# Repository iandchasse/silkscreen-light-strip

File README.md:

# Silkscreen light strip

> [!IMPORTANT]
> **AI-generated design. This is an accessory, not part of the Silkscreen PCBA.**
>
> This light strip was designed with substantial AI assistance: its KiCad project is generated by scripts written with
> AI tools. It serves two purposes: a test of what AI tools can and cannot do with a simple electrical design like an
> LED strip, and a functional accessory for the base Silkscreen PCBA. The Silkscreen PCBA itself
> ([silkscreen-pcb](https://github.com/iandchasse/silkscreen-pcb)) was not AI-generated.
>
> See Silkscreen's AI disclosure: https://silkscreenreader.com/ai

**A DIY warm/cool reading light for the [Silkscreen](https://github.com/iandchasse/silkscreen-pcb) e-reader.** It is a thin flex PCB that plugs into the main board's frontlight connector (labelled `J3` on the back of the board), in place of a panel's bonded frontlight. It runs six warm/cool pairs of side-emitting LEDs along the left edge of the e-paper panel, and the light grazes across the page with no light guide.

**One strip fits two readers:**

- the **4.26″** plain `GDEY0426T82`, where the LED bar lies on the panel's left border;
- the **3.68″** 528 × 792 panel of the x3 build, where the bar lies beside the glass and the top pair folds back under it.

**Not released.** The website does not offer the strip or its cases. This repo is the design, its fabrication files and its documents, for anyone who wants to build one.

**The cases** are in [silkscreen-enclosures](https://github.com/iandchasse/silkscreen-enclosures). Each reader's case project can also build a light-strip case, which the strip needs: the tub, and on the 3.68″ also the four bottom keys. Those cases are in development and not released either (see [The cases](#the-cases)).

**Where things are:**

| To | Go to |
|---|---|
| **Order the light strip (rev A, untested)** | [`production/`](production/) and [docs/ORDERING.md](docs/ORDERING.md) |
| **Assemble and fit the strip** | [docs/ASSEMBLY.md](docs/ASSEMBLY.md) |
| **Print a paste stencil** and its card squeegee, one plate (experimental, untested) | [`production/stencil/`](production/stencil/) (`stencil-kit_*.3mf`) and [docs/ASSEMBLY.md §2, option](docs/ASSEMBLY.md#option-3d-printed-paste-stencil-and-oven-reflow-experimental-untested) |
| **The cases** | the light-strip builds in [silkscreen-enclosures](https://github.com/iandchasse/silkscreen-enclosures) (`enclosures/case-426`, `enclosures/case-368`), in development with the strip |
| **Change the strip** | `tools/` (it generates the KiCad project at the root and everything in `docs/` and `production/`); the design is in [docs/DESIGN.md](docs/DESIGN.md) |
| **Read the documents** | the [documents index](#documents) below: design, ordering, assembly, reports, research and reviews |

> **Rev A is untested.** The strip passes ERC, DRC and schematic parity with no findings. Four review rounds have been worked through ([docs/DESIGN.md §8](docs/DESIGN.md#8-verification) lists them; the first round's reports are in [docs/review/](docs/review/)). No board has been built yet. Before you solder a whole strip, diode-test one loose LED ([docs/ASSEMBLY.md](docs/ASSEMBLY.md#1-check-led-polarity-before-anything-else)).

| Flat, LED side (turned 90°) |
|:---:|
|  |

| 4.26″: on the border, around the glass edge | 4.26″: behind the board, into the frontlight connector |
|:---:|:---:|
|  |  |

| 3.68″: beside the panel | 3.68″: top pair folded back under the bar | 3.68″: spare tail looped on the board's back |
|:---:|:---:|:---:|
|  |  |  |

## What it is

- **Where it goes.** The LED bar runs along the panel's left long edge, hidden under the bezel. The strip then sweeps along the bottom border and folds over the bottom glass edge, through the main board's FPC slot, and plugs into the frontlight connector on the back of the board. The fold follows the path of the stock frontlight ribbon.
  - **On the 4.26″** the bar is taped onto the panel's border, and the tail wraps the glass edge in a U.
  - **On the 3.68″** the smaller panel leaves the bar beside its glass, on a shelf in the front shell at the panel-front plane. The tail folds over the glass edge straight into the slot.
- **Light.** There are twelve XINGLIGHT side-view LEDs: six `XL-4008WWC` (3000 K) and six `XL-4008UWC` (6000–6500 K). Each is 4.0 × 1.4 mm and 0.8 mm tall. They sit in six tight warm/cool pairs, 6.6 mm apart within a pair, so both colours light the same patch of page. Each LED's face points across the screen, parallel to its surface.
- **Two readers, one layout.**
  - The bottom five pairs are 15.55 mm apart, which is the 3.68″ active height divided by five.
  - The top pair sits 17.0 mm above them, on its own stiffener piece, with a 3.6 mm bare **hinge** in between.
  - On the 4.26″ all six pairs light the screen.
  - On the 3.68″ the top pair would stick out past the case, so it folds back under the bar, tape to tape, and its light is hidden.
- **Electrically, it is a stock frontlight.**
  - Each colour is one series string of 6 LEDs, about 17.4 V at 13.3 mA, or about 18.4 V at the driver including the flip-protection diode.
  - Worst case (−10 °C, top Vf bin) is 21.7 V, under the 22 V design ceiling and the driver's 24.25 V over-voltage limit. A high batch (LCSC lists the cool LED at 3.4 V) can pass 22 V in the cold, still under the over-voltage limit; check one string on the bench ([docs/DESIGN.md §2.1](docs/DESIGN.md#21-six-leds-per-string)).
  - The main board's TPS923610 does everything: constant current, dimming and warm/cool select. Only the firmware's "strip open" threshold changes (see below).
- **Flip-proof.** The frontlight connector contacts both faces of a tail, so a tail inserted face-down would mirror the pins. A BAV70W per string blocks that case. The strip stays dark, the driver latches its over-voltage protection, and no LED is reverse-stressed.
- **Built to survive handling.**
  - The bar ends in a full round. Every turn of the outline is a sweeping radius of 1.6–4 mm, and the outer corners span the foot's full 3.5 mm height. Only two places stay small: the contact tab's R0.2 tip corners, which Hirose specifies, and one 1 mm inside corner on the stiffener.
  - The folding section is 5.5 mm wide and carries four 0.4 mm conductors on one copper layer. It has no vias, pads or stiffener, and a copper tear-stop rail runs along each edge.
  - The hinge has no vias, pads, stiffener or tape; its tracks run straight across it.

| | |
|---|---|
| Flat size | 15.1 × 127.6 mm (bar 2.3 mm wide, foot 3.5 mm, tail 5.5 mm, contact tab 3.5 mm over the last 3.8 mm) |
| Build | 2-layer flex, 0.11 mm, 25 µm adhesiveless polyimide, black coverlay, ENIG |
| Stiffeners | PI 0.225 mm in three pieces: the top pair, the bar and foot, and the last 14 mm of the tail (0.30 mm at the contacts). 3M 9077 tape on the two front pieces. |
| Driver output | About 18.4 V typical; 15.9–21.7 V across LED bins and −10 to 60 °C, including the flip-protection diode |
| Current | 13.3 mA nominal and 13.9 mA maximum, set by the main board's 15 Ω current-set resistor (`R37`). One string at a time. |
| Connector | Gold fingers for the main board's frontlight connector (`J3`), a Hirose FH34SRJ-6S-0.5SH(50). Pins: 1 LED_SW, 2 C−, 3/4 NC, 5 LED_SW, 6 W−. |
| Parts | 12 LEDs and 2 BAV70W, plus three wire/probe pads on the tail (`S`, `C`, `W`) |

## Bill of materials

| Qty | Ref | Part | Manufacturer | LCSC |
|---|---|---|---|---|
| 6 | D1–D6 | XL-4008WWC, warm 3000 K side-view LED | XINGLIGHT | C5440667 |
| 6 | D7–D12 | XL-4008UWC, cool 6000–6500 K side-view LED | XINGLIGHT | C2843774 |
| 2 | D13, D14 | BAV70W,115, dual common-cathode diode, SOT-323 | Nexperia | C28064 |

These three LCSC parts are all JLCPCB "Extended" parts. The LEDs are sold only through LCSC. The BAV70W is also a stock DigiKey part.

## The cases

**The light-strip cases are in development and are not released.** The website does not offer them, and no case has been printed around a strip yet. Both readers' cases are in [silkscreen-enclosures](https://github.com/iandchasse/silkscreen-enclosures) (`enclosures/case-426` and `enclosures/case-368`; until 2026-10-21 they lived in this repo). Each project builds a **standard** case and a **light-strip** case, and the two builds share every printed part except:

| | 4.26″ (`enclosures/case-426`) | 3.68″ (`enclosures/case-368`) |
|---|---|---|
| Panel | Plain GDEY0426T82 instead of the FT01C | The x3's 3.68″ panel |
| Differs from the standard build | The tub only | The tub and the four bottom keys (`key-x3ls` stands 0.8 mm taller than `key-x3std`, for the raised face); 13.7 mm deep |
| Front shell | Stops for the thinner plain panel; a raised ceiling over the left border; hold-down pads between the pairs; a wider ribbon gap | Front raised 1.2 mm over x3's, 0.8 over the standard build's (still one flat face); a channel for the bar with the light path to the window; hold-down pads; a neck gap in the chin |

Each case project carries a copy of this strip's outline and fold geometry (`hardware/reference/light-strip/strip-geometry.json`, from `build/geometry.json` here, a git-ignored file that `tools/export_geometry.py` writes with KiCad's Python); [docs/DESIGN.md §4](docs/DESIGN.md#4-geometry-and-fold) has the geometry.

## Using it

### Order it

[docs/ORDERING.md](docs/ORDERING.md) has every file and every field. In short:

- **Files.** Upload `production/silkscreen-light-strip_rev-A_gerbers.zip` to JLCPCB's flex order. It holds the copper, coverlay, silkscreen, paste, outline and drill files, plus the two extra layers `Stiffener_PI0_225.gbr` and `Adhesive_3M9077.gbr`. The bend-zone layer stays out. `production/jlc_bom.csv` and `jlc_cpl.csv` are for an assembled order only; `production/bom.csv` is the parts list for a hand build or an LCSC order; `production/gerbers/` has the loose files, the job file and the drill map.
- **The form.** Flex, 2 layers, quantity 5, FPC 0.11 mm, 1/3 oz copper, black coverlay, white silkscreen, ENIG (1 U″; 2 U″ if you expect to re-insert the tail often), EDA software "Other", stiffener **Polyimide 0.225 mm + 3M Tape 3M9077** selected together in one row, tape pull tab yes (at the foot end), **gold fingers yes, 0.295 mm**, no EMI film, laser cutting, **confirm production file yes**. Paste the 190-character remark from ORDERING.md as it is: JLC does not read the stiffener or tape layers by itself.
- **Bare, soldered by hand** is the recommended path for rev A: it is cheap, and it lets you do the polarity test first. JLC assembly is possible (Panel by JLCPCB, Standard PCBA, a $23.57 fixture and three Extended-part fees); check each LED's window direction and anode position in the preview, not the polarity dot.
- **Cost** is an unverified ballpark only: about $45–75 for 5 bare strips, plus shipping, and about $65–95 more to have JLC assemble 2 of them.

### Assemble and fit

[docs/ASSEMBLY.md](docs/ASSEMBLY.md) covers the polarity check, soldering, a bench test through the three pads (`S`, `C`, `W`), which reader and which case, the fit on the 4.26″ (on the border) and on the 3.68″ (beside the panel, with the top pair folded back), plugging into the frontlight connector, the case, firmware bring-up and troubleshooting.

### Firmware

- Drive it exactly like the stock frontlight ([silkscreen-pcb HARDWARE.md §7](https://github.com/iandchasse/silkscreen-pcb/blob/master/docs/HARDWARE.md#7-frontlight-driver)).
- Enable `ADIM` (`PWM_LED`, IO42) with a HIGH pulse of at least 100 µs (the datasheet minimum is 40 µs), then dim with PWM at 10–200 kHz.
- Change the colour with `COLOR_SEL` (IO40) only while the PWM duty is 0. Keep that pause under about 1 ms, or send the enable pulse again.
- Watch `LED_MONIT` (IO2). A lit strip reads 1.4–2.4 V at full duty.
  - **Open, flipped or missing:** the peak over the first ~1 s after enabling is **2.49 V or more**. The old 2.2 V threshold would call a cold six-LED strip open.
  - The driver then latches off, and `LED_MONIT` sinks back to the off level over several seconds, so record the fault when you first see it.
  - **Shorted LEDs or a bridge:** below 1.30 V at full duty, at least 50 ms after enabling.
  - To restart after a latch, hold `ADIM` low for at least 3 ms.

## What to expect from the light

Light that grazes a page falls off steeply with distance. The geometric model in `tools/optics_sim.py` puts the irradiance 2 mm in from the lit edge at about 230 times the far edge on the 4.26″, and at about 10 times the far edge 20 mm in. The textured front film of an e-paper panel scatters grazing light, which flattens this in practice. The page will still be brighter on the left than the right.

- **On the 4.26″,** six pairs light the edge more evenly than the first layout's five. The ripple along the edge 6 mm in drops from 3.7:1 to 3.1:1.
- **On the 3.68″,** the LED faces are 2.37 mm from the image instead of 1.2 mm. That softens the bright band at the edge; the ripple 3 mm in drops to 5:1.

| Model, one string lit (4.26″ left, 3.68″ right) | Falloff across the page |
|:---:|:---:|
|  |  |

## Documents

| Document | What |
|---|---|
| [`docs/DESIGN.md`](docs/DESIGN.md) | Why the strip is as it is: the main-board fixes, the electrical design (six LEDs per string, the firmware thresholds, the two diodes), the LEDs, the geometry and fold on both readers, robustness, optics, the flex build and DFM, verification and open items. It is current where the dated notes differ. |
| [`docs/ORDERING.md`](docs/ORDERING.md) | The JLCPCB flex order: the files, the form field by field, the remark, the production-file review, bare or assembled, a cost ballpark and a checklist before you pay (also the Fabrication Toolkit route) |
| [`docs/ASSEMBLY.md`](docs/ASSEMBLY.md) | The LED polarity test, soldering, the bench test, which reader and case, fitting on the 4.26″ and the 3.68″, plugging into the frontlight connector, the case, firmware bring-up and troubleshooting |
| [`docs/reports/stencil_slice_check.md`](docs/reports/stencil_slice_check.md) | The paste stencil's slicer read-back: apertures open, membrane printed, pocket empty, print time and filament (toolpath only; nothing has been printed) |
| [`docs/reports/stencil_plate_check.md`](docs/reports/stencil_plate_check.md) | The two stencil-kit projects (`production/stencil/stencil-kit_*.3mf`) read back from a slice: parts and positions, project settings, openings clear on all three cards, the squeegee, the coupon, print time and filament (toolpath only; nothing has been printed) |
| [`docs/reports/stencil_squeegee_check.md`](docs/reports/stencil_squeegee_check.md) | The squeegee's slicer read-back: slot, slits and screw hole open, blade layers, bridges, no floating islands, print time (toolpath only; nothing has been printed) |
| [`docs/reports/design_summary.md`](docs/reports/design_summary.md) | The as-built numbers, regenerated by `tools/report_design.py` on every build |
| [`docs/reports/erc.rpt`](docs/reports/erc.rpt), [`drc.rpt`](docs/reports/drc.rpt) (and `.json`) | The ERC and DRC (with schematic parity) reports from `tools/make_outputs.py`; zero findings |
| [`docs/silkscreen-light-strip_schematic.pdf`](docs/silkscreen-light-strip_schematic.pdf), [`_layout.pdf`](docs/silkscreen-light-strip_layout.pdf) | The schematic, and the layout one layer per page |
| [`docs/mechanical/`](docs/mechanical/) | The flat strip in 3D (`silkscreen-light-strip_flat.step` and `.wrl`) |
| [`docs/images/`](docs/images/) | Renders (flat, folded into each reader, night view), the optics heatmaps and profile, and `optics_summary.json` |
| [`docs/research/electrical-limits.md`](docs/research/electrical-limits.md) (with [`electrical-limits-calc.py`](docs/research/electrical-limits-calc.py)) | Dated 2026-09-24: string voltage and current limits against the TPS923610, cited |
| [`docs/research/fpc-and-jlc-flex.md`](docs/research/fpc-and-jlc-flex.md) | Dated 2026-09-24: the Hirose FH34SRJ tail specification and JLCPCB's flex capabilities |
| [`docs/research/leds.md`](docs/research/leds.md) | Dated 2026-09-24: a survey of side-view warm and cool LEDs on LCSC, and why the XL-4008 pair |
| [`docs/research/mechanical-fit.md`](docs/research/mechanical-fit.md) | Dated 2026-09-24: how the strip fits the board and panel, with the coordinate frames |
| [`docs/review/electrical.md`](docs/review/electrical.md) | Review of 2026-09-25: polarity, nets, the voltage budget, flip and fault behaviour |
| [`docs/review/dfm.md`](docs/review/dfm.md) | Review of 2026-09-25: JLC flex manufacturability and the order files |
| [`docs/review/kicad.md`](docs/review/kicad.md) | Review of 2026-09-25: project integrity, reproducibility and tooling |

The research and review notes are dated records; `docs/DESIGN.md` is current where they differ.

## Repository

| Path | What |
|---|---|
| `silkscreen-light-strip.kicad_pro/.kicad_sch/.kicad_pcb` | The KiCad 9 project. It is generated, but you can open and edit it like any other project. |
| `lib/` | Project footprints, symbols and 3D models: the LED (VRML plus a STEP body), the contact tail for the frontlight connector, SOT-323 and the wire pad |
| `production/` | `*_gerbers.zip` for the flex order, plus `jlc_bom.csv`, `jlc_cpl.csv`, `bom.csv` and `gerbers/` |
| `production/stencil/` | The 3D-printable paste stencil for the 24 LED pads: three print STLs (pocket depth 0.3, 0.4, 0.5 mm), a STEP, an optional test coupon, the two one-plate kit projects `stencil-kit_cc2.3mf` and `stencil-kit_generic.3mf` (all three cards, the squeegee with its blades and the coupon, written by OrcaSlicer), `stencil_params.json` and the extracted pad data; and the squeegee that wipes the paste on (`squeegee_print.stl`, a spare PLA blade, `squeegee_params.json`). Experimental, untested. |
| `fabrication-toolkit-options.json` | Settings for the Fabrication Toolkit plugin, if you make the order files with it instead ([ORDERING.md](docs/ORDERING.md#with-the-fabrication-toolkit-plugin)) |
| `docs/` | Schematic and layout PDFs, `DESIGN.md`, `ASSEMBLY.md`, `ORDERING.md`, renders, `mechanical/` (flat STEP/VRML), `reports/` (ERC/DRC/as-built summary), `research/`, `review/` |
| `tools/params.py` | Every dimension and part choice in one file, including both panels, the pair layout and the hinge |
| `tools/generate.py`, `build_pcb.py`, `kigeom.py`, `make_step_model.py` | Write the footprints, symbols, schematic, project and board (and the LED's STEP body). The layout is built from the schematic's own netlist. |
| `tools/make_outputs.py` | ERC, DRC with parity, Gerbers and drill, BOM and CPL, PDFs, STEP, renders. It fails if any check finds anything. |
| `tools/stencil/` | The paste stencil: `extract_paste.py` (KiCad Python, reads the pads and outline from a copy of the board), `stencil.py` (CadQuery: the card, the STLs and their checks), `slice_check.py` (slices with the OrcaSlicer command line and reads the G-code back, writes `docs/reports/stencil_slice_check.md`), `squeegee.py` (CadQuery: the squeegee handle and blade, its checks and its slice read-back, writes `docs/reports/stencil_squeegee_check.md`), `make_plate.py` (has the OrcaSlicer command line write the two kit projects and reads them back from a slice, writes `docs/reports/stencil_plate_check.md` and `docs/images/stencil_plate_*.png`), `render.py` (the `docs/images/stencil_*.png` pictures) |
| `tools/report_design.py` | Writes the as-built summary, `docs/reports/design_summary.md` |
| `tools/foldpath.py` | Tail length each reader needs, over a tolerance sweep |
| `tools/optics_sim.py` | Grazing-light irradiance model for both panels |
| `tools/blender_fold.py`, `export_geometry.py` | Fold the real outline into either reader in Blender for the renders above |

### Regenerating

Close the project in KiCad first; the generator refuses to run while KiCad holds a lock file. Then run these in PowerShell (on another system, use KiCad 9's Python the same way):

```powershell
& "C:\Program Files\KiCad\9.0\bin\python.exe" tools\generate.py
```

```powershell
& "C:\Program Files\KiCad\9.0\bin\python.exe" tools\make_outputs.py
```

Set `KICAD9_DIR` and `KICAD_CLI` if KiCad is installed somewhere else.

- **Fold renders:** run `tools/export_geometry.py` with KiCad's Python (it writes the git-ignored `build/geometry.json`), then `blender -b -P tools/blender_fold.py -- 64 426` and `-- 64 368`. This needs Blender.
- **Optics model:** `tools/optics_sim.py` needs numpy and matplotlib.
- **After a geometry change:** first run `tools/export_geometry.py` with KiCad's Python, which writes `build/geometry.json` (git-ignored, so it is not in a fresh clone), then copy that file into both case projects of silkscreen-enclosures, as `enclosures/case-426/hardware/reference/light-strip/strip-geometry.json` and `enclosures/case-368/hardware/reference/light-strip/strip-geometry.json`, and rebuild those cases (that repo's `enclosures/README.md`, "Rebuilding"). If `tools/optics_sim.py`'s heatmap changes, copy `docs/images/optics_heatmaps.png` there too (the showcase uses it).

The layout is generated, so GUI edits to the `.kicad_pcb` are overwritten the next time `generate.py` runs. Make changes in `tools/params.py` or `tools/build_pcb.py`, or stop using the generator and edit the board by hand from then on.

## Related

- [silkscreen-pcb](https://github.com/iandchasse/silkscreen-pcb): the main board, including the frontlight connector (`J3`) and the TPS923610 driver ([HARDWARE.md §7](https://github.com/iandchasse/silkscreen-pcb/blob/master/docs/HARDWARE.md#7-frontlight-driver)).
- [silkscreen-enclosures](https://github.com/iandchasse/silkscreen-enclosures): the cases; the light-strip builds are in development.
- [silkscreen-light-attachment](https://github.com/iandchasse/silkscreen-light-attachment): a different light, a clip-on bar that plugs into the main board's expansion header (`J6`), for a reader with nothing in the frontlight connector. The two are alternatives.
- [silkscreenreader.com](https://silkscreenreader.com): the Silkscreen site. It does not offer the strip.

## License

CERN-OHL-S-2.0, © 2026 idc LLC. See [LICENSE](LICENSE) and [NOTICE](NOTICE).

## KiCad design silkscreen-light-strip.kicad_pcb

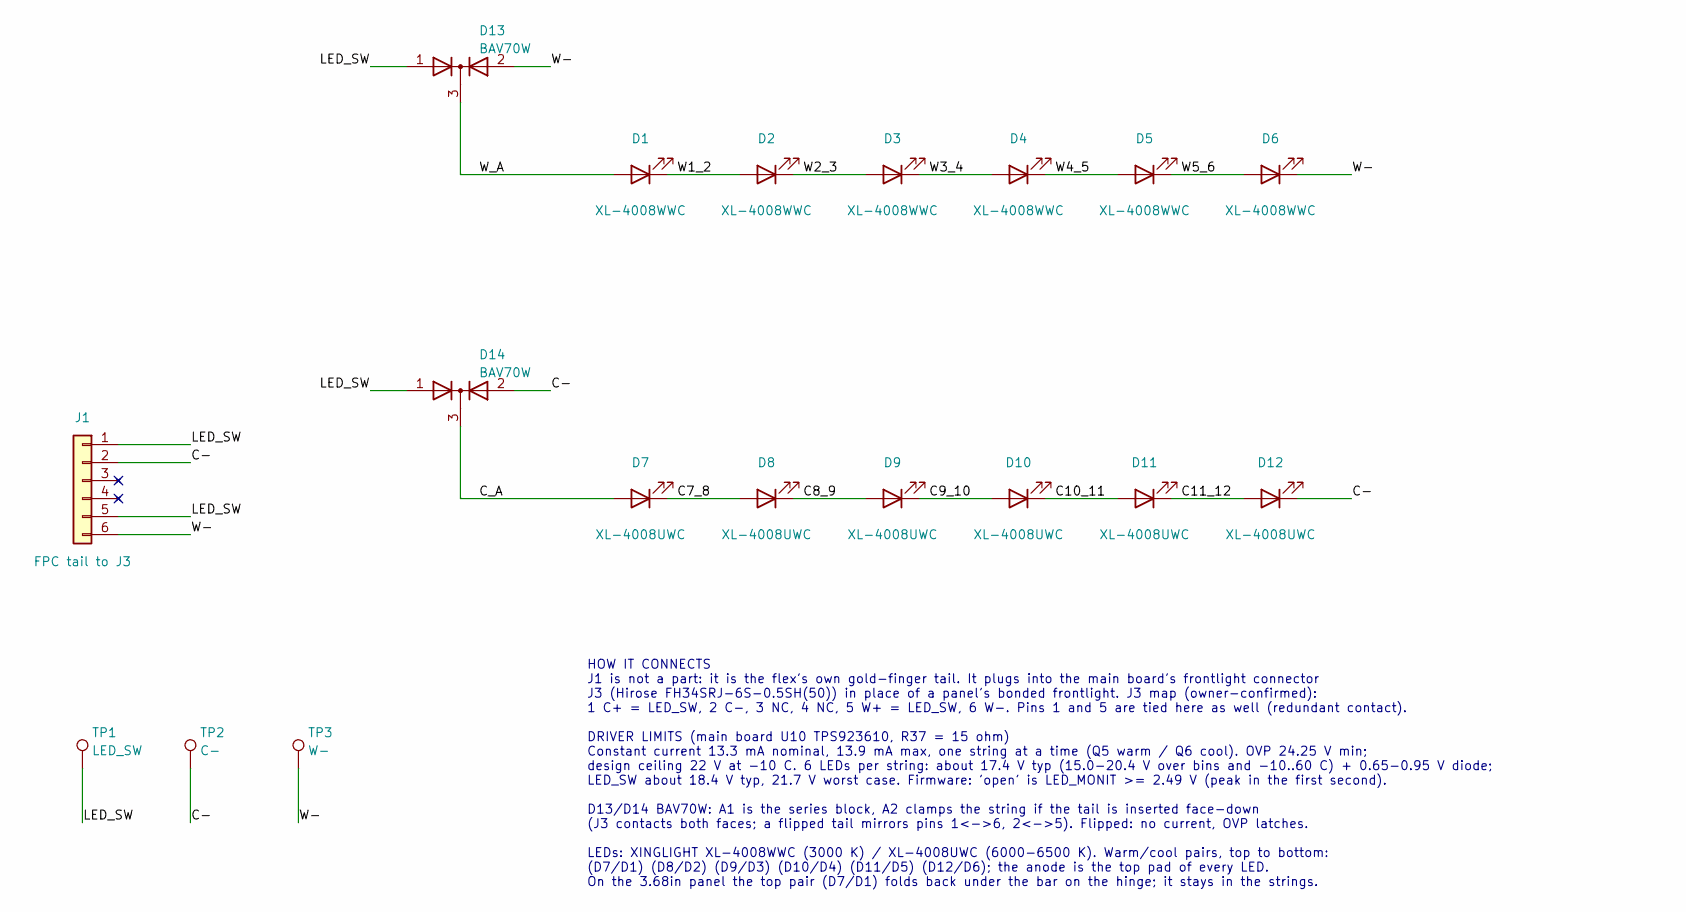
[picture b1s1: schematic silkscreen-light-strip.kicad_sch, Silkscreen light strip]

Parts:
D1, D2, D3, D4, D5, D6: XL-4008WWC; LED_SideView_XINGLIGHT_XL-4008; MPN XL-4008WWC; LCSC C5440667
D7, D8, D9, D10, D11, D12: XL-4008UWC; LED_SideView_XINGLIGHT_XL-4008; MPN XL-4008UWC; LCSC C2843774
D13, D14: BAV70W; SOT-323_SC-70; MPN BAV70W,115; LCSC C28064
J1: FPC tail to J3; FPC_Tail_FH34SRJ_6P_P0.50mm_TopContact
TP1: LED_SW; TestPad_0.8mm_Wire
TP2: C-; TestPad_0.8mm_Wire
TP3: W-; TestPad_0.8mm_Wire

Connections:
/C7_8: D7.1 (K), D8.2 (A)
/C8_9: D8.1 (K), D9.2 (A)
/C9_10: D9.1 (K), D10.2 (A)
/C10_11: D10.1 (K), D11.2 (A)
/C11_12: D11.1 (K), D12.2 (A)
/C-: D12.1 (K), D14.2 (A), J1.2 (C-), TP2.1
/C_A: D7.2 (A), D14.3 (K)
/LED_SW: D13.1 (A), D14.1 (A), J1.1 (LED_SW(C+)), J1.5 (LED_SW(W+)), TP1.1
/W1_2: D1.1 (K), D2.2 (A)
/W2_3: D2.1 (K), D3.2 (A)
/W3_4: D3.1 (K), D4.2 (A)
/W4_5: D4.1 (K), D5.2 (A)
/W5_6: D5.1 (K), D6.2 (A)
/W-: D6.1 (K), D13.2 (A), J1.6 (W-), TP3.1
/W_A: D1.2 (A), D13.3 (K)

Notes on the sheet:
HOW IT CONNECTS J1 is not a part: it is the flex's own gold-finger tail. It plugs into the main board's frontlight connector J3 (Hirose FH34SRJ-6S-0.5SH(50)) in place of a panel's bonded frontlight. J3 map (owner-confirmed): 1 C+ = LED_SW, 2 C-, 3 NC, 4 NC, 5 W+ = LED_SW, 6 W-. Pins 1 and 5 are tie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

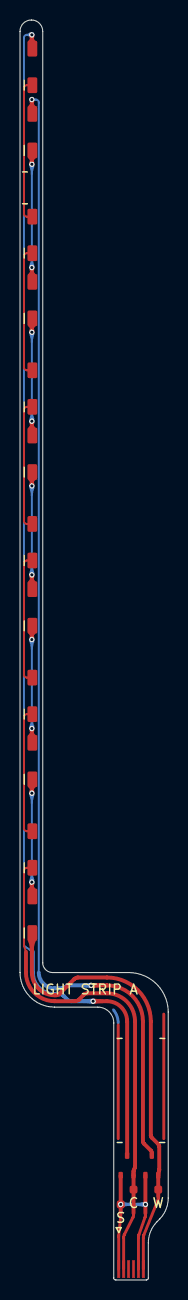
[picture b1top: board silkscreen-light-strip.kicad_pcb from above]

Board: 2 copper layers, 15.0 x 127.5 mm, 18 parts (0 on the bottom side), 15 nets.

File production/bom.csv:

Qty,Designators,Value,Manufacturer,MPN,LCSC,Footprint,Description
6,"D1,D2,D3,D4,D5,D6",XL-4008WWC,XINGLIGHT,XL-4008WWC,C5440667,LED_SideView_XINGLIGHT_XL-4008,"Warm white 3000 K side-view LED, 4.0x1.4x0.8 mm"
6,"D7,D8,D9,D10,D11,D12",XL-4008UWC,XINGLIGHT,XL-4008UWC,C2843774,LED_SideView_XINGLIGHT_XL-4008,"Cool white 6000-6500 K side-view LED, 4.0x1.4x0.8 mm"
2,"D13,D14",BAV70W,Nexperia,"BAV70W,115",C28064,SOT-323_SC-70,D13: Warm string: series block + reverse clamp (flip protection); D14: Cool string: series block + reverse clamp (flip protection)

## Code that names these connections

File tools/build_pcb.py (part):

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# ---------------------------------------------------------------- back run (behind the main board)
Y_STIFF = TIP - T["stiffener_back"]                    # 154.665: start of the back-run PI stiffener
Y_DIODE = Y_STIFF + 2.40                               # SOT-323 row (rot 90: pin 3 up, pins 1/2 down)
DC_AT = (COL["C_A"], Y_DIODE)                          # cool BAV70W: pin3 <- C_A, pin1 SW = LED_SW, pin2 SE = C-
DW_AT = (COL["C_A"] + 2.50, Y_DIODE)                   # warm BAV70W (0.55 web to the cool one): pin3 <- W_A, pin1 SW = LED_SW, pin2 SE = W-
Y_TP = Y_DIODE + 2.45                                  # C- and W- test pads (0.5 web to the diodes); the LED_SW pad sits 1.5 mm lower
Y_TAPER0 = Y_TP + 2.1                                  # the 5.5 mm tail eases into the 3.5 mm tab below here
FINGER_OF = {"LED_SW_a": 1, "C-": 2, "LED_SW_b": 5, "W-": 6}
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    return {1: (at[0] - 0.65, at[1] + 1.0), 2: (at[0] + 0.65, at[1] + 1.0), 3: (at[0], at[1] - 1.0)}[n]


TP_AT = {"TP1": (sot_pin(DC_AT, 1)[0], Y_TP + 1.5),   # LED_SW (staggered: 0.5 mm coverlay web to TP2)
         "TP2": (sot_pin(DC_AT, 2)[0], Y_TP),         # C-
         "TP3": (sot_pin(DW_AT, 2)[0], Y_TP)}         # W-

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

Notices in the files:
silkscreen-light-strip.kicad_pcb:
Licensed under CERN-OHL-S-2.0
(c) 2026 idc LLC
